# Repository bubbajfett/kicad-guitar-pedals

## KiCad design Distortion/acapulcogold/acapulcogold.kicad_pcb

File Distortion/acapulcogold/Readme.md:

# Acapulco Gold Distorgion

This is a clone of the Earthquaker Devices acapulco gold distortion pedal.

It is base on  a pair of LM386 op-amps, and provides a very crunchy distortion.

So this pedal is verified. I have not boxed this one yet, either.

All trademarks belong to their respective owners.

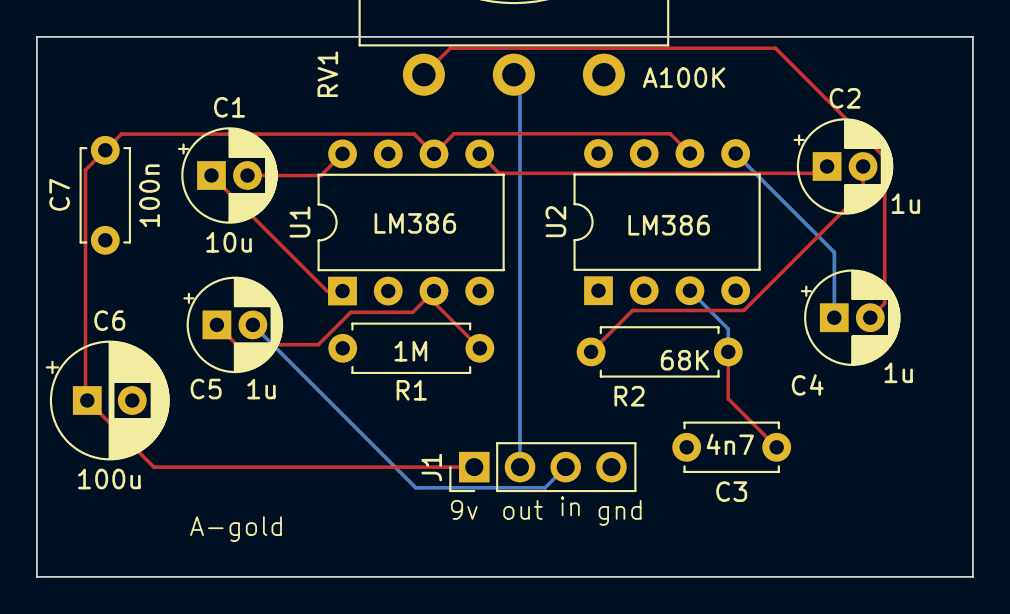
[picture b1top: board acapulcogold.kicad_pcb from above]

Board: 2 copper layers, 52.0 x 30.0 mm, 13 parts (0 on the bottom side), 12 nets.

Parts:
C1: 10u; CP_Radial_D5.0mm_P2.00mm
C2, C4, C5: 1u; CP_Radial_D5.0mm_P2.00mm
C3: 4n7; C_Disc_D5.0mm_W2.5mm_P5.00mm
C6: 100u; CP_Radial_D6.3mm_P2.50mm
C7: 100n; C_Disc_D5.0mm_W2.5mm_P5.00mm
J1: Conn_01x04_Pin; PinHeader_1x04_P2.54mm_Vertical
R1: 1M; R_Axial_DIN0207_L6.3mm_D2.5mm_P7.62mm_Horizontal
R2: 68K; R_Axial_DIN0207_L6.3mm_D2.5mm_P7.62mm_Horizontal
RV1: A100K; Potentiometer_Omeg_PC16BU_Vertical
U1, U2: LM386; DIP-8_W7.62mm

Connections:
GND: C3.2, C6.2, C7.1, J1.4, R1.2, RV1.1, U1.2 (-), U1.4 (GND), U2.2 (-), U2.4 (GND)
unnamed: C1.1, U1.1 (GAIN)
unnamed: C1.2, U1.8 (GAIN)
unnamed: C2.1, U1.5
unnamed: C2.2, R2.1
unnamed: C4.1, U2.5
unnamed: C4.2, RV1.3
unnamed: C5.1, R1.1, U1.3 (+)
unnamed: C3.1, R2.2, U2.3 (+)
in: C5.2, J1.3
out: J1.2, RV1.2
vcc: C6.1, C7.2, J1.1, U1.6 (V+), U2.6 (V+)

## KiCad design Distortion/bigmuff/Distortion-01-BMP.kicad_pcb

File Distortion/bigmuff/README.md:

# big muff

Distortion pedal, loosely based on BMP

Two PCB layouts now, one is for unclear version of BMP, and the
other based on the ramshead version.   Both sound pretty
much the same to me.   The
ramshead version uses different potentiometer form-factor (RK09).  

Both are verified.

Requires KICAD 7

Build doc is [here](./bigmuff.pdf)

All trademarks are owned by their respective owners.

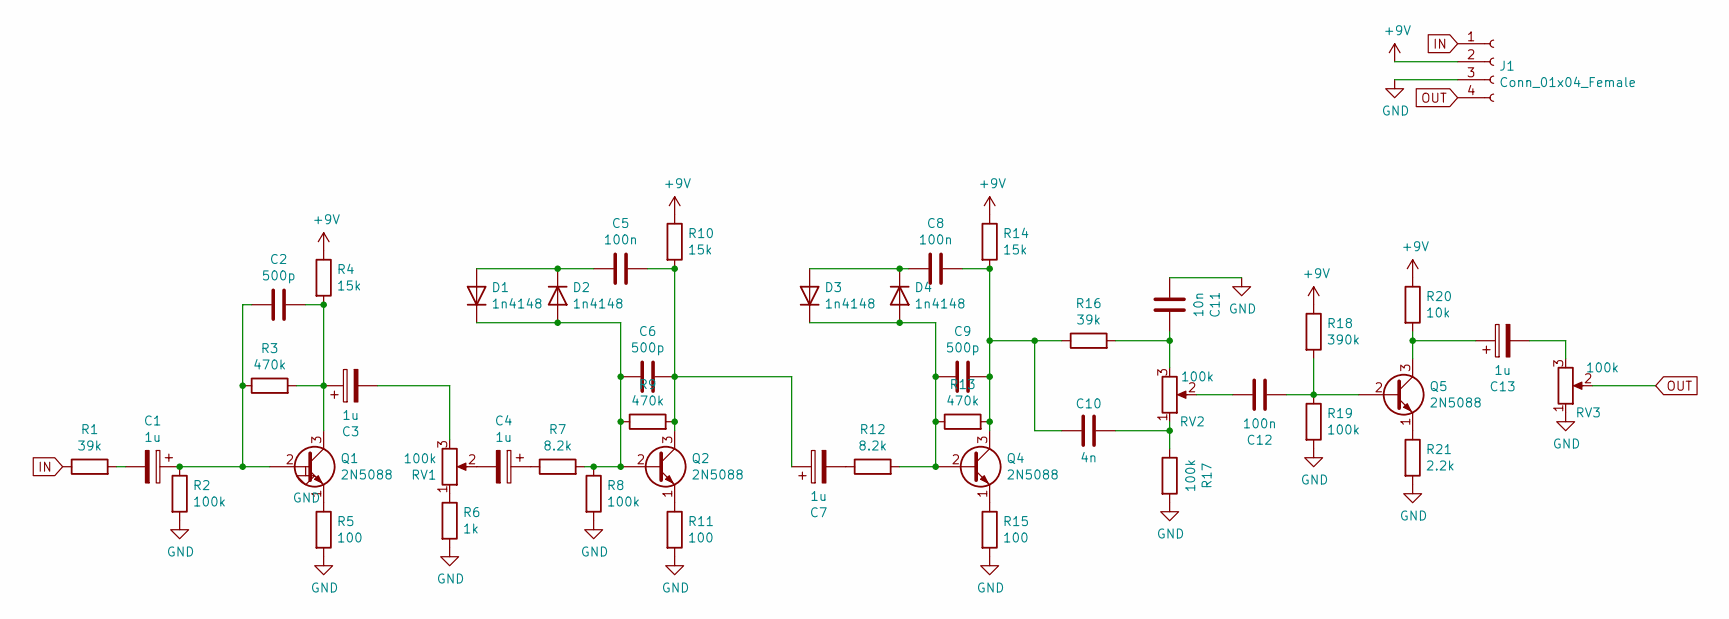
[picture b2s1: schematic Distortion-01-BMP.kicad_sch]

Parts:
C1, C3, C4, C7, C13: 1u; CP_Radial_D5.0mm_P2.00mm
C2, C6, C9: 500p; C_Disc_D7.5mm_W2.5mm_P5.00mm
C5, C8, C12: 100n; C_Disc_D7.5mm_W2.5mm_P5.00mm
C10: 4n; C_Disc_D7.5mm_W2.5mm_P5.00mm
C11: 10n; C_Disc_D7.5mm_W2.5mm_P5.00mm
D1, D2, D3, D4: 1n4148; D_A-405_P7.62mm_Horizontal
J1: Conn_01x04_Female; PinHeader_1x04_P2.54mm_Vertical
Q1, Q2, Q4, Q5: 2N5088; TO-92_Inline
R1, R16: 39k; R_Axial_DIN0207_L6.3mm_D2.5mm_P10.16mm_Horizontal
R2, R8, R17, R19: 100k; R_Axial_DIN0207_L6.3mm_D2.5mm_P10.16mm_Horizontal
R3, R9, R13: 470k; R_Axial_DIN0207_L6.3mm_D2.5mm_P10.16mm_Horizontal
R4, R10, R14: 15k; R_Axial_DIN0207_L6.3mm_D2.5mm_P10.16mm_Horizontal
R5, R11, R15: 100; R_Axial_DIN0207_L6.3mm_D2.5mm_P10.16mm_Horizontal
R6: 1k; R_Axial_DIN0207_L6.3mm_D2.5mm_P10.16mm_Horizontal
R7, R12: 8.2k; R_Axial_DIN0207_L6.3mm_D2.5mm_P10.16mm_Horizontal
R18: 390k; R_Axial_DIN0207_L6.3mm_D2.5mm_P10.16mm_Horizontal
R20: 10k; R_Axial_DIN0207_L6.3mm_D2.5mm_P10.16mm_Horizontal
R21: 2.2k; R_Axial_DIN0207_L6.3mm_D2.5mm_P10.16mm_Horizontal
RV1, RV2, RV3: 100k; Potentiometer_Omeg_PC16BU_Vertical

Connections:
+9V: J1.2, R4.1, R10.1, R14.1, R18.1, R20.1
GND: C11.2, J1.3, R2.2, R5.2, R6.2, R8.2, R11.2, R15.2, R17.2, R19.2, R21.2, RV3.1
IN: J1.1, R1.1
unnamed: C1.1, C2.2, Q1.2 (B), R2.1, R3.1
unnamed: C1.2, R1.2
unnamed: C2.1, C3.1, Q1.3 (C), R3.2, R4.2
unnamed: C3.2, RV1.3
unnamed: C4.1, R7.1
unnamed: C4.2, RV1.2
unnamed: C5.1, C6.1, C7.1, Q2.3 (C), R9.2, R10.2
unnamed: C5.2, D1.2 (A), D2.1 (K)
unnamed: C6.2, D1.1 (K), D2.2 (A), Q2.2 (B), R7.2, R8.1, R9.1
unnamed: C7.2, R12.1
unnamed: C8.2, D3.2 (A), D4.1 (K)
unnamed: C9.2, D3.1 (K), D4.2 (A), Q4.2 (B), R12.2, R13.1
unnamed: C10.1, R17.1, RV2.1
unnamed: C8.1, C9.1, C10.2, Q4.3 (C), R13.2, R14.2, R16.1
unnamed: C11.1, R16.2, RV2.3
unnamed: C12.1, RV2.2
unnamed: C12.2, Q5.2 (B), R18.2, R19.1
unnamed: C13.1, Q5.3 (C), R20.2
unnamed: C13.2, RV3.3
unnamed: Q1.1 (E), R5.1
unnamed: Q2.1 (E), R11.1
unnamed: Q4.1 (E), R15.1
unnamed: Q5.1 (E), R21.1
unnamed: R6.1, RV1.1
OUT: J1.4, RV3.2

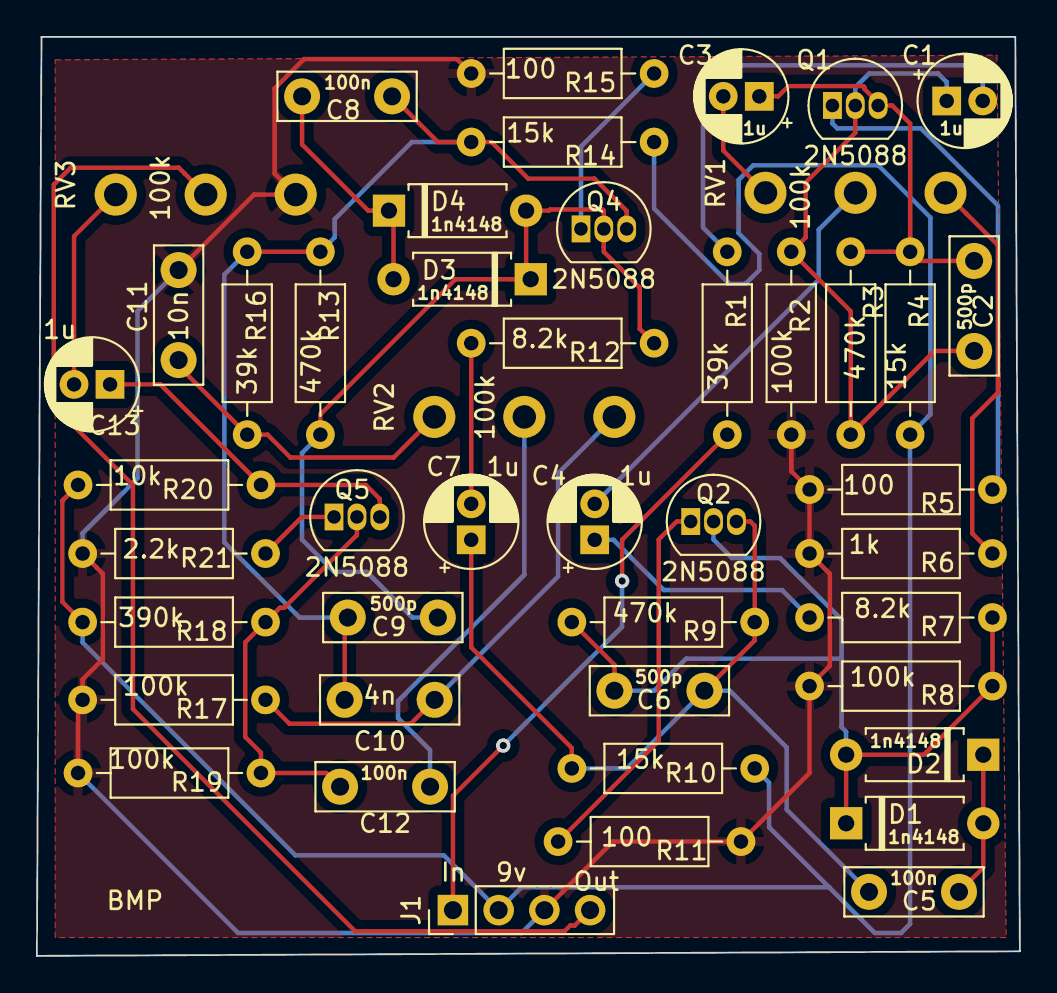
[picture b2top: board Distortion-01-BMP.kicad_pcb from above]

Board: 2 copper layers, 54.6 x 51.1 mm, 46 parts (0 on the bottom side), 28 nets.

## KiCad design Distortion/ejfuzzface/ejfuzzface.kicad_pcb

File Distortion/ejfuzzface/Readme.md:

# EJ Fuzz Face

This is a clone of the Eric Johnson fuzz face.   Very nice sound, and gets very
crunchy when first in the chain.

This is the 2nd version of the pedal.   The first version had the fuzz pot without a ground connection 

So this pedal circuit  is verified.  I hate using a 125B box on something
this small but my last attempt at boxing top-jacks on a 1590B did not work very well.

Anyway, all trademarks belong to their respective owners.

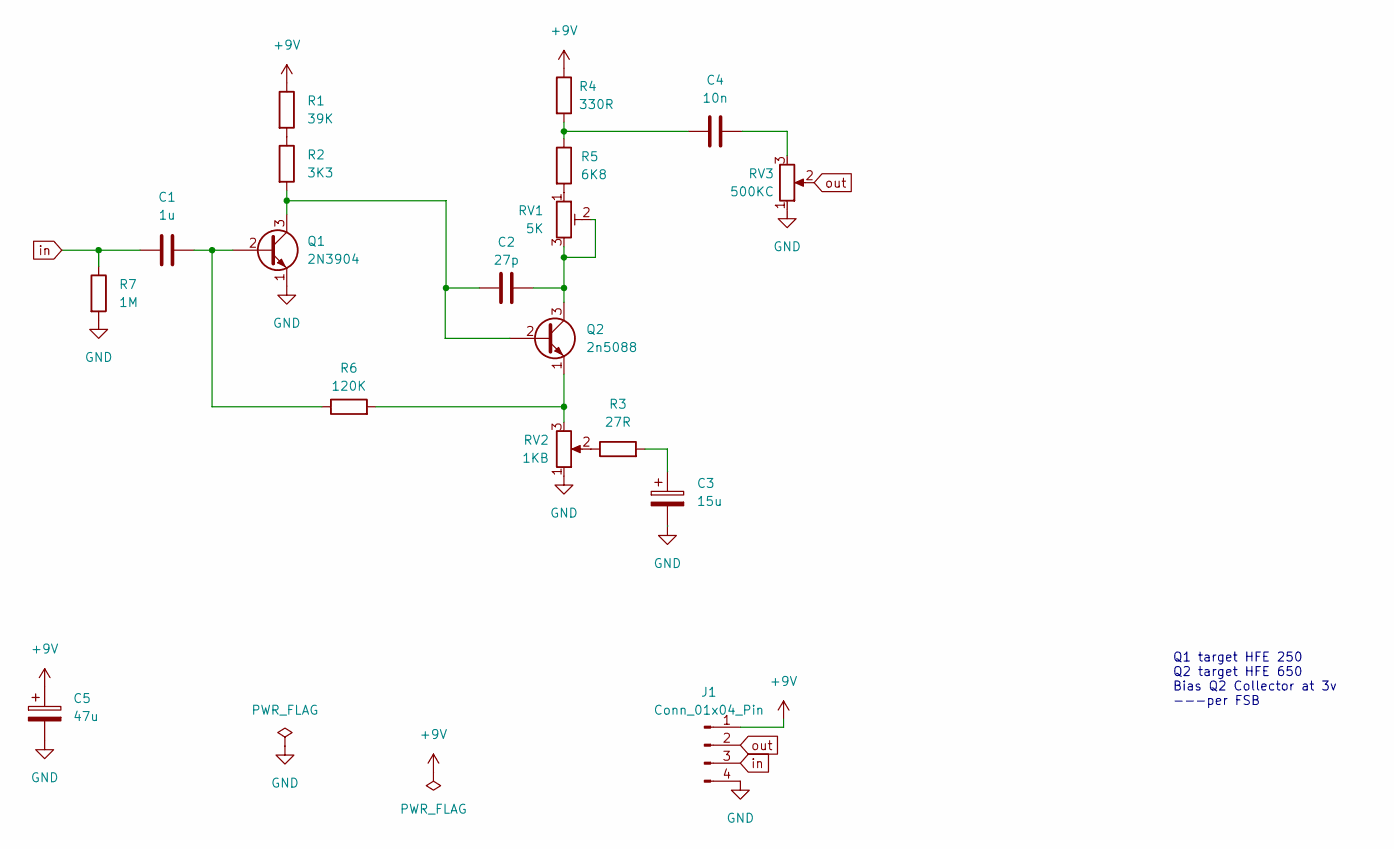
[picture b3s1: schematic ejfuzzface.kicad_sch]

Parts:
C1: 1u; C_Rect_L7.0mm_W2.0mm_P5.00mm
C2: 27p; C_Disc_D5.0mm_W2.5mm_P2.50mm
C3: 15u; CP_Radial_D6.3mm_P2.50mm
C4: 10n; C_Rect_L7.0mm_W2.0mm_P5.00mm
C5: 47u; CP_Radial_D6.3mm_P2.50mm
J1: Conn_01x04_Pin; PinHeader_1x04_P2.54mm_Vertical
Q1: 2N3904; TO-92_Inline
Q2: 2n5088; TO-92_Inline
R1: 39K; R_Axial_DIN0207_L6.3mm_D2.5mm_P10.16mm_Horizontal
R2: 3K3; R_Axial_DIN0207_L6.3mm_D2.5mm_P10.16mm_Horizontal
R3: 27R; R_Axial_DIN0207_L6.3mm_D2.5mm_P10.16mm_Horizontal
R4: 330R; R_Axial_DIN0207_L6.3mm_D2.5mm_P10.16mm_Horizontal
R5: 6K8; R_Axial_DIN0207_L6.3mm_D2.5mm_P10.16mm_Horizontal
R6: 120K; R_Axial_DIN0207_L6.3mm_D2.5mm_P10.16mm_Horizontal
R7: 1M; R_Axial_DIN0207_L6.3mm_D2.5mm_P10.16mm_Horizontal
RV1: 5K; Potentiometer_Runtron_RM-065_Vertical
RV2: 1KB; Pot_Underside
RV3: 500KC; Pot_Underside

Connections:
+9V: C5.1, J1.1, R1.1, R4.1
GND: C3.2, C5.2, J1.4, Q1.1 (E), R7.2, RV2.1, RV3.1
unnamed: C3.1, R3.2
unnamed: C4.1, R4.2, R5.1
unnamed: C4.2, RV3.3
unnamed: C1.2, Q1.2 (B), R6.1
unnamed: C2.1, Q1.3 (C), Q2.2 (B), R2.2
unnamed: C2.2, Q2.3 (C), RV1.2, RV1.3
unnamed: Q2.1 (E), R6.2, RV2.3
unnamed: R1.2, R2.1
unnamed: R3.1, RV2.2
unnamed: R5.2, RV1.1
in: C1.1, J1.3, R7.1
out: J1.2, RV3.2

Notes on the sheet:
Q1 target HFE 250 Q2 target HFE 650 Bias Q2 Collector at 3v ---per FSB

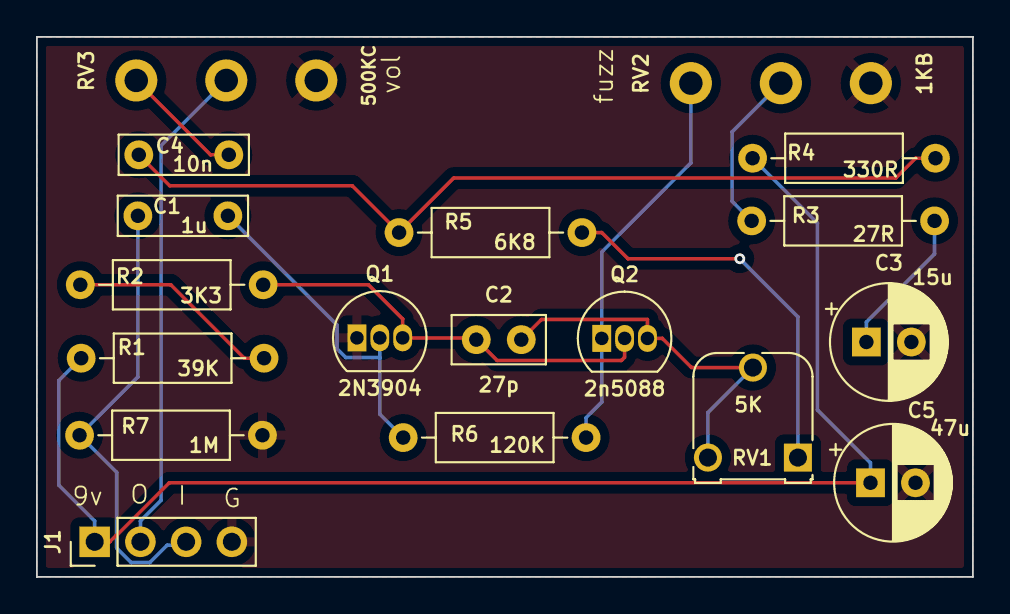
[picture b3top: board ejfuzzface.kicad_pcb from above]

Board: 2 copper layers, 52.0 x 30.0 mm, 18 parts (0 on the bottom side), 14 nets.

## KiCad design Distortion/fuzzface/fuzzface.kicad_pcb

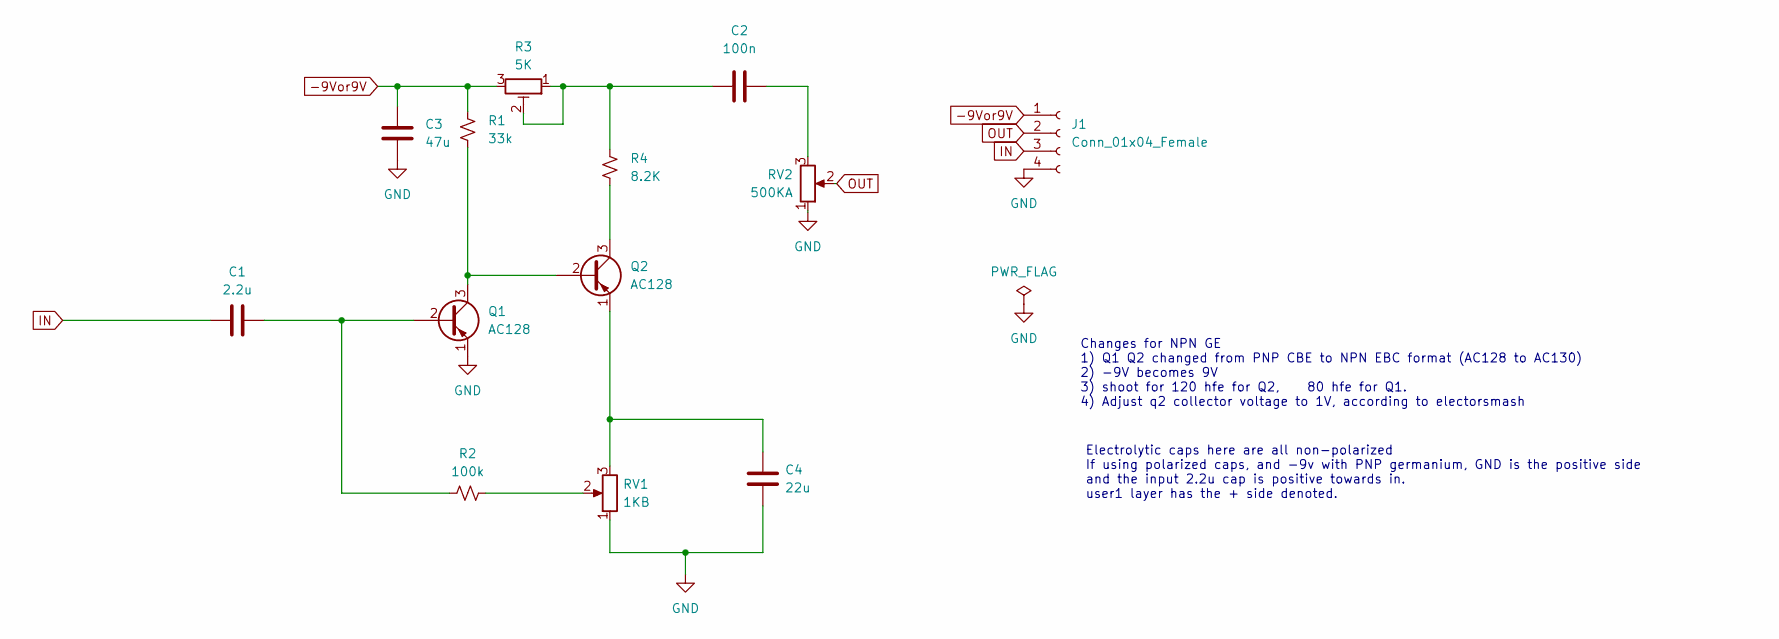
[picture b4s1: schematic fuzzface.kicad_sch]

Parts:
C1: 2.2u; C_Radial_D5.0mm_H5.0mm_P2.00mm
C2: 100n; C_Rect_L7.0mm_W3.5mm_P5.00mm
C3: 47u; C_Radial_D6.3mm_H7.0mm_P2.50mm
C4: 22u; C_Radial_D6.3mm_H7.0mm_P2.50mm
J1: Conn_01x04_Female; PinHeader_1x04_P2.54mm_Vertical
Q1, Q2: AC128; PinHeader_1x03_P2.54mm_Vertical
R1: 33k; R_Axial_DIN0207_L6.3mm_D2.5mm_P10.16mm_Horizontal
R2: 100k; R_Axial_DIN0207_L6.3mm_D2.5mm_P10.16mm_Horizontal
R3: 5K; Potentiometer_Runtron_RM-065_Vertical
R4: 8.2K; R_Axial_DIN0207_L6.3mm_D2.5mm_P10.16mm_Horizontal
RV1: 1KB; 16MM_PCB_PADS
RV2: 500KA; 16MM_PCB_PADS

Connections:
-9Vor9V: C3.1, J1.1, R1.2, R3.3
GND: C3.2, C4.2, J1.4, Q1.1 (E), RV1.1, RV2.1
IN: C1.1, J1.3
unnamed: C2.1, R3.1, R3.2, R4.2
unnamed: C2.2, RV2.3
unnamed: C1.2, Q1.2 (B), R2.1
unnamed: Q1.3 (C), Q2.2 (B), R1.1
unnamed: Q2.3 (C), R4.1
unnamed: C4.1, Q2.1 (E), RV1.3
unnamed: R2.2, RV1.2
OUT: J1.2, RV2.2

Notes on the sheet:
Electrolytic caps here are all non-polarized If using polarized caps, and -9v with PNP germanium, GND is the positive side and the input 2.2u cap is positive towards in. user1 layer has the + side denoted.
Changes for NPN GE 1) Q1 Q2 changed from PNP CBE to NPN EBC format (AC128 to AC130) 2) -9V becomes 9V 3) shoot for 120 hfe for Q2, 80 hfe for Q1. 4) Adjust q2 collector voltage to 1V, according to electorsmash

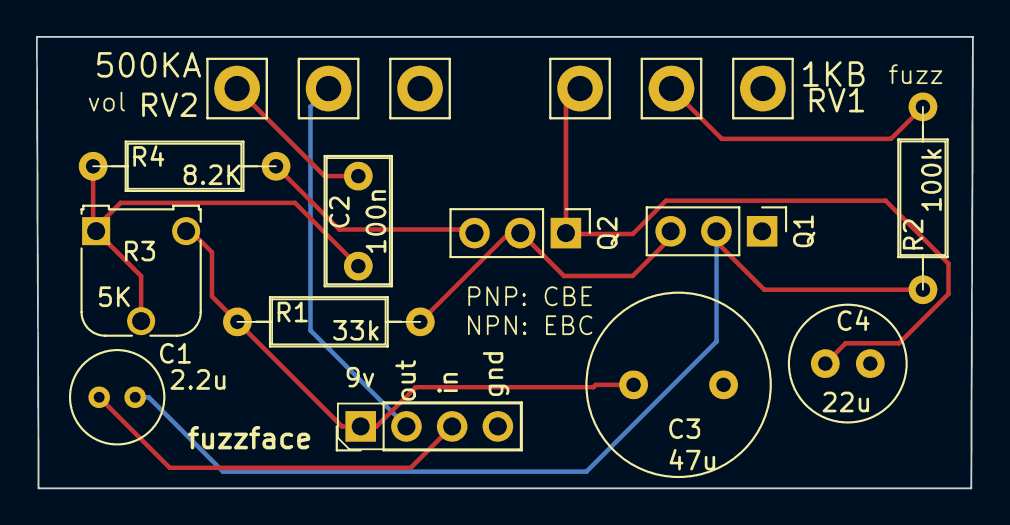
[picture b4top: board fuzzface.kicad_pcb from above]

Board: 2 copper layers, 52.0 x 25.1 mm, 13 parts (0 on the bottom side), 11 nets.

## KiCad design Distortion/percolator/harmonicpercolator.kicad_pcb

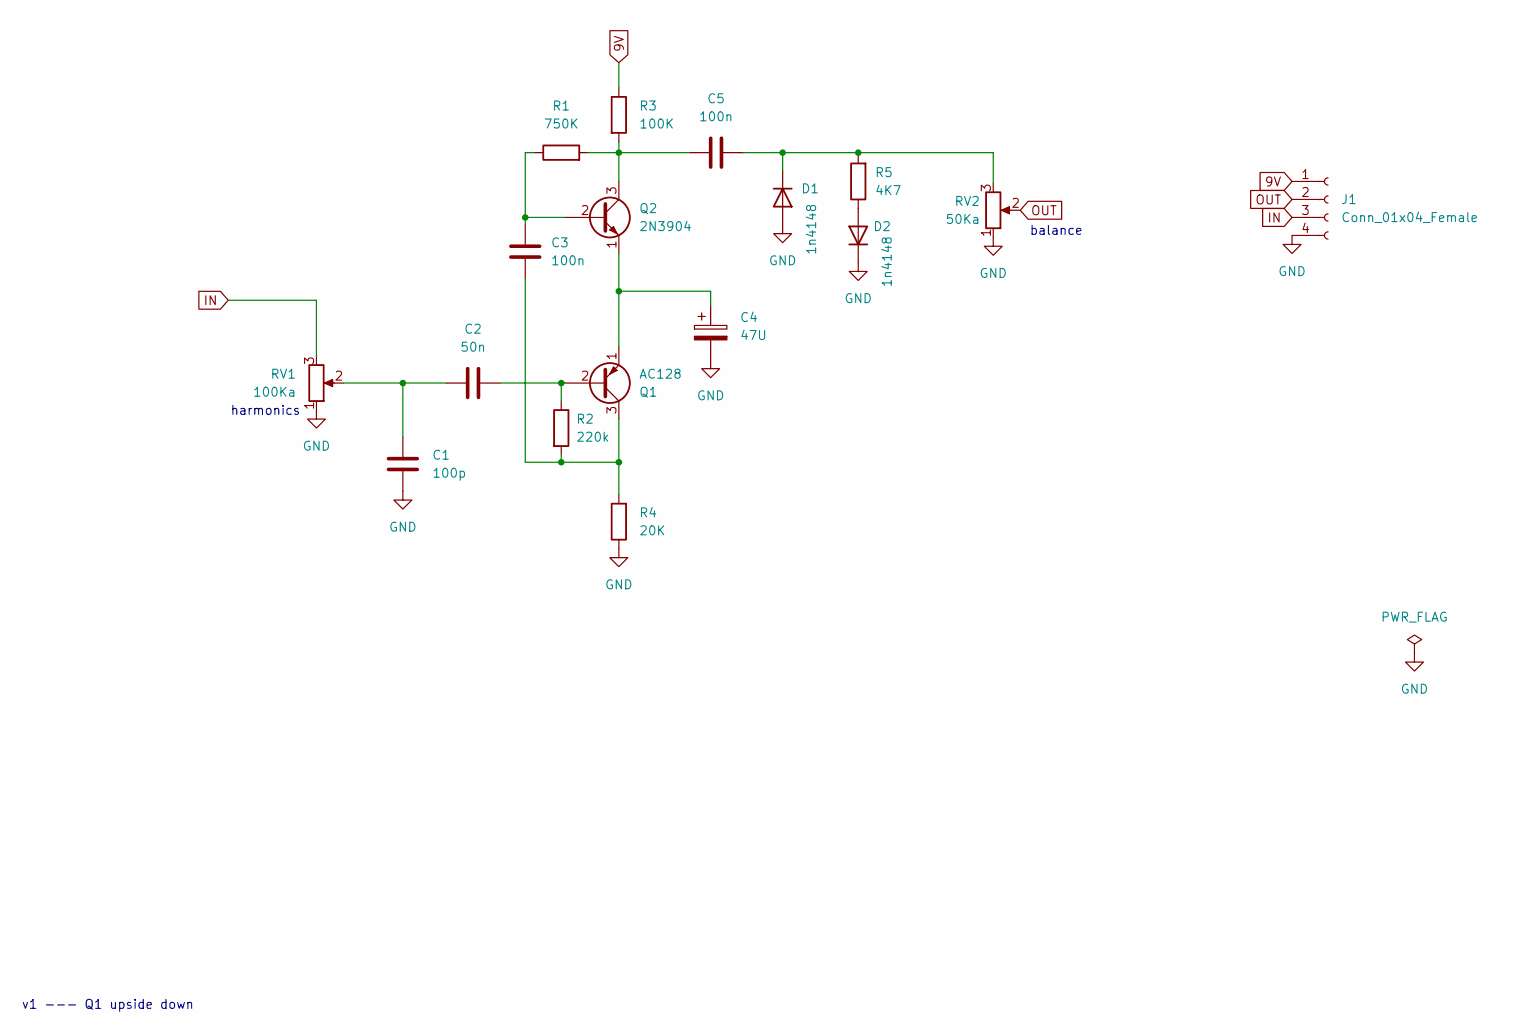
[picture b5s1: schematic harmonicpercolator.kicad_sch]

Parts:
C1: 100p; C_Disc_D5.0mm_W2.5mm_P2.50mm
C2: 50n; C_Disc_D7.5mm_W2.5mm_P5.00mm
C3, C5: 100n; C_Disc_D7.5mm_W2.5mm_P5.00mm
C4: 47U; CP_Radial_D5.0mm_P2.50mm
D1, D2: 1n4148; D_A-405_P7.62mm_Horizontal
J1: Conn_01x04_Female; PinHeader_1x04_P2.54mm_Vertical
Q1: AC128; TO-5-3
Q2: 2N3904; TO-92_Inline
R1: 750K; R_Axial_DIN0207_L6.3mm_D2.5mm_P7.62mm_Horizontal
R2: 220k; R_Axial_DIN0207_L6.3mm_D2.5mm_P7.62mm_Horizontal
R3: 100K; R_Axial_DIN0207_L6.3mm_D2.5mm_P7.62mm_Horizontal
R4: 20K; R_Axial_DIN0207_L6.3mm_D2.5mm_P7.62mm_Horizontal
R5: 4K7; R_Axial_DIN0207_L6.3mm_D2.5mm_P7.62mm_Horizontal
RV1: 100Ka; Pot_Underside
RV2: 50Ka; Pot_Underside

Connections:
9V: J1.1, R3.1
GND: C1.2, C4.2, D1.2 (A), D2.1 (K), J1.4, R4.1, RV1.1, RV2.1
IN: J1.3, RV1.3
unnamed: C1.1, C2.1, RV1.2
unnamed: C5.1, D1.1 (K), R5.2, RV2.3
unnamed: D2.2 (A), R5.1
unnamed: C2.2, Q1.2 (B), R2.1
unnamed: C3.1, Q1.3 (C), R2.2, R4.2
unnamed: C4.1, Q1.1 (E), Q2.1 (E)
unnamed: C3.2, Q2.2 (B), R1.1
unnamed: C5.2, Q2.3 (C), R1.2, R3.2
OUT: J1.2, RV2.2

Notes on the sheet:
balance
harmonics
v1 --- Q1 upside down

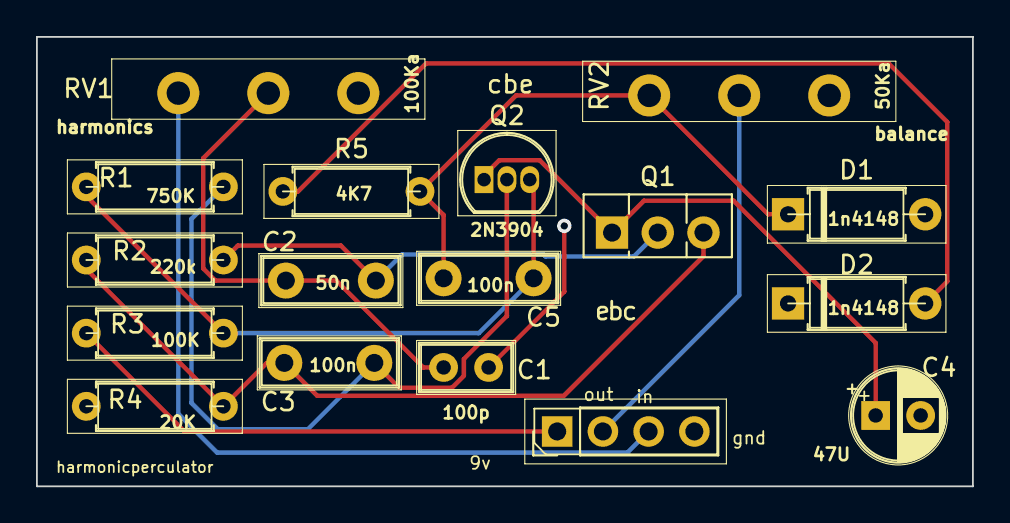
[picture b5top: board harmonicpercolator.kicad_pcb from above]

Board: 2 copper layers, 52.0 x 25.0 mm, 17 parts (0 on the bottom side), 12 nets.

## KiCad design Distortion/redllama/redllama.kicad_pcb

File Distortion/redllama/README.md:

Distortion pedal, loosely based on the red llama pedal.

This is unverified.

All trademarks belong to their respective trademark owners.

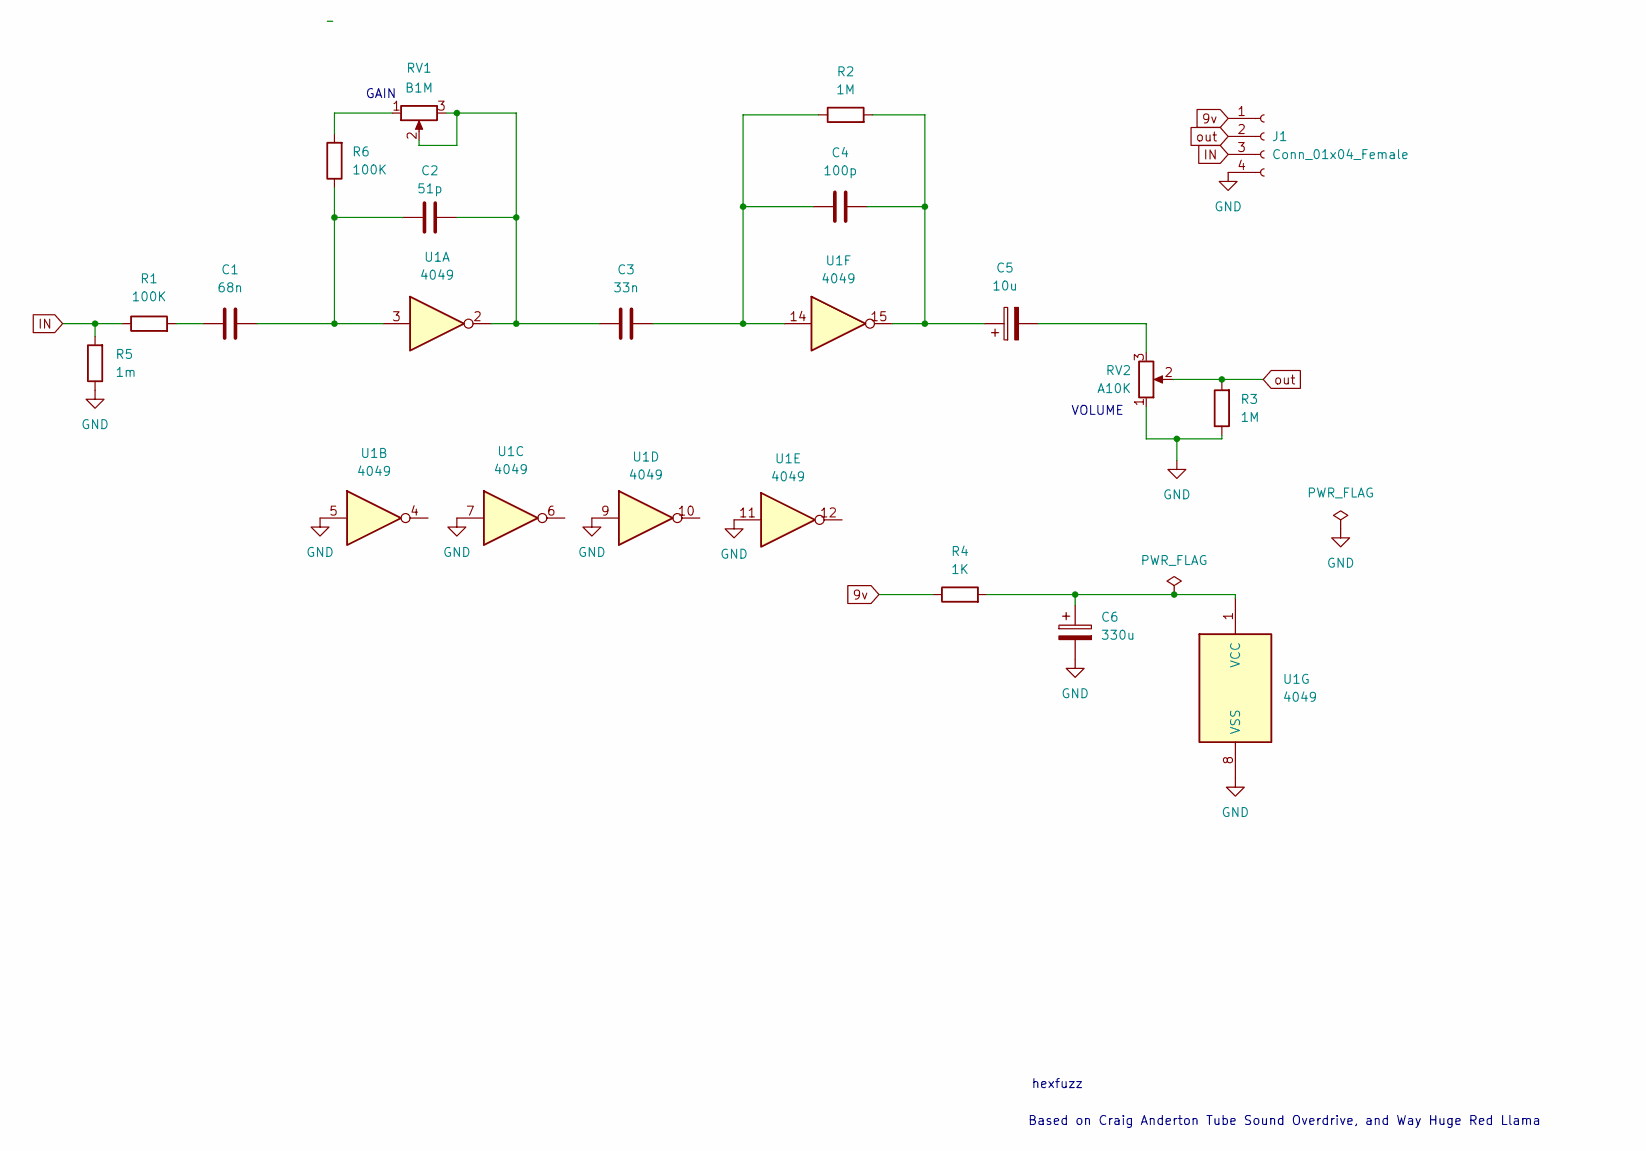
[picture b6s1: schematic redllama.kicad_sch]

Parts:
C1: 68n; C_Rect_L7.0mm_W2.5mm_P5.00mm
C2: 51p; C_Disc_D3.8mm_W2.6mm_P2.50mm
C3: 33n; C_Rect_L7.0mm_W2.5mm_P5.00mm
C4: 100p; C_Disc_D3.8mm_W2.6mm_P2.50mm
C5: 10u; CP_Radial_D5.0mm_P2.00mm
C6: 330u; CP_Radial_D7.5mm_P2.50mm
J1: Conn_01x04_Female; PinHeader_1x04_P2.54mm_Vertical
R1, R6: 100K; R_Axial_DIN0207_L6.3mm_D2.5mm_P7.62mm_Horizontal
R2, R3: 1M; R_Axial_DIN0207_L6.3mm_D2.5mm_P7.62mm_Horizontal
R4: 1K; R_Axial_DIN0207_L6.3mm_D2.5mm_P7.62mm_Horizontal
R5: 1m; R_Axial_DIN0207_L6.3mm_D2.5mm_P7.62mm_Horizontal
RV1: B1M; Pot_Underside
RV2: A10K; Pot_Underside
U1: 4049; DIP-16_W7.62mm

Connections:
9v: J1.1, R4.1
GND: C6.2, J1.4, R3.1, R5.1, RV2.1, U1.5, U1.7, U1.8 (VSS), U1.9, U1.11
IN: J1.3, R1.1, R5.2
unnamed: C1.1, R1.2
unnamed: C1.2, C2.1, R6.1, U1.3
unnamed: C2.2, C3.1, RV1.2, RV1.3, U1.2
unnamed: C3.2, C4.1, R2.1, U1.14
unnamed: C4.2, C5.1, R2.2, U1.15
unnamed: C5.2, RV2.3
unnamed: R6.2, RV1.1
unnamed: C6.1, R4.2, U1.1 (VCC)
out: J1.2, R3.2, RV2.2

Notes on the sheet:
GAIN
Based on Craig Anderton Tube Sound Overdrive, and Way Huge Red Llama
hexfuzz
VOLUME

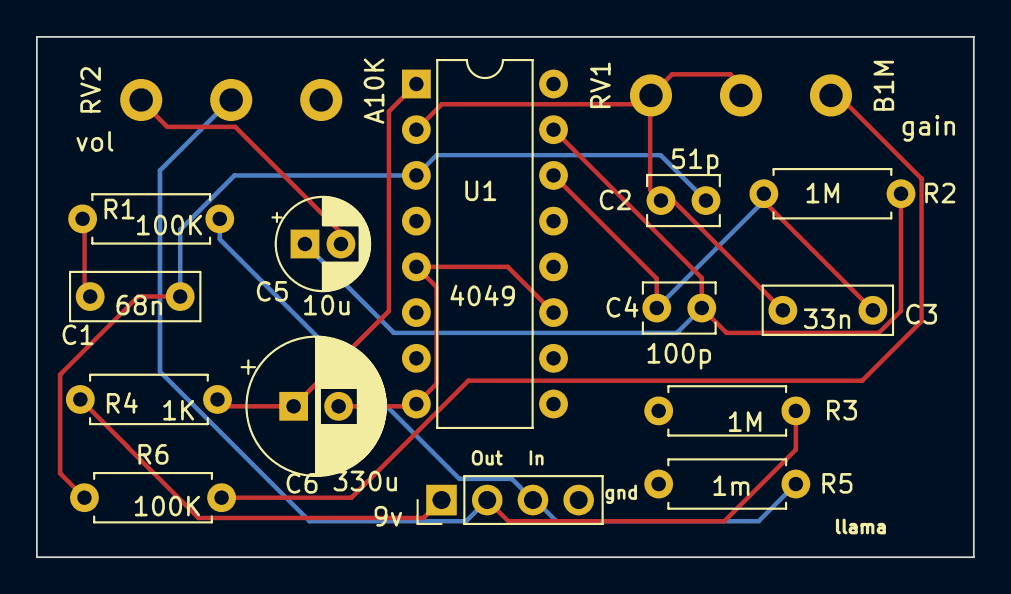
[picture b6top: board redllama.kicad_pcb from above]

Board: 2 copper layers, 52.1 x 28.9 mm, 16 parts (0 on the bottom side), 12 nets.

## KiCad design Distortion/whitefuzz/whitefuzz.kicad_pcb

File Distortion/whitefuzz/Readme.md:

# whitefuzz

This pedal is based on the Bearfoot FX artic white fuzz, which is apparently somewhat based on the fuzzface

First build used 2n5457 and while it made a distortion sound, it was
very clippy.  Researching other (dirtboxlayout, effectslayout,
pedalpcb) forums, the recommendation was to use J113 (and a couple
other jfets I did not have).  Replacing this made this sound so much
better.

All registered trademarks are owned by their respective owners.

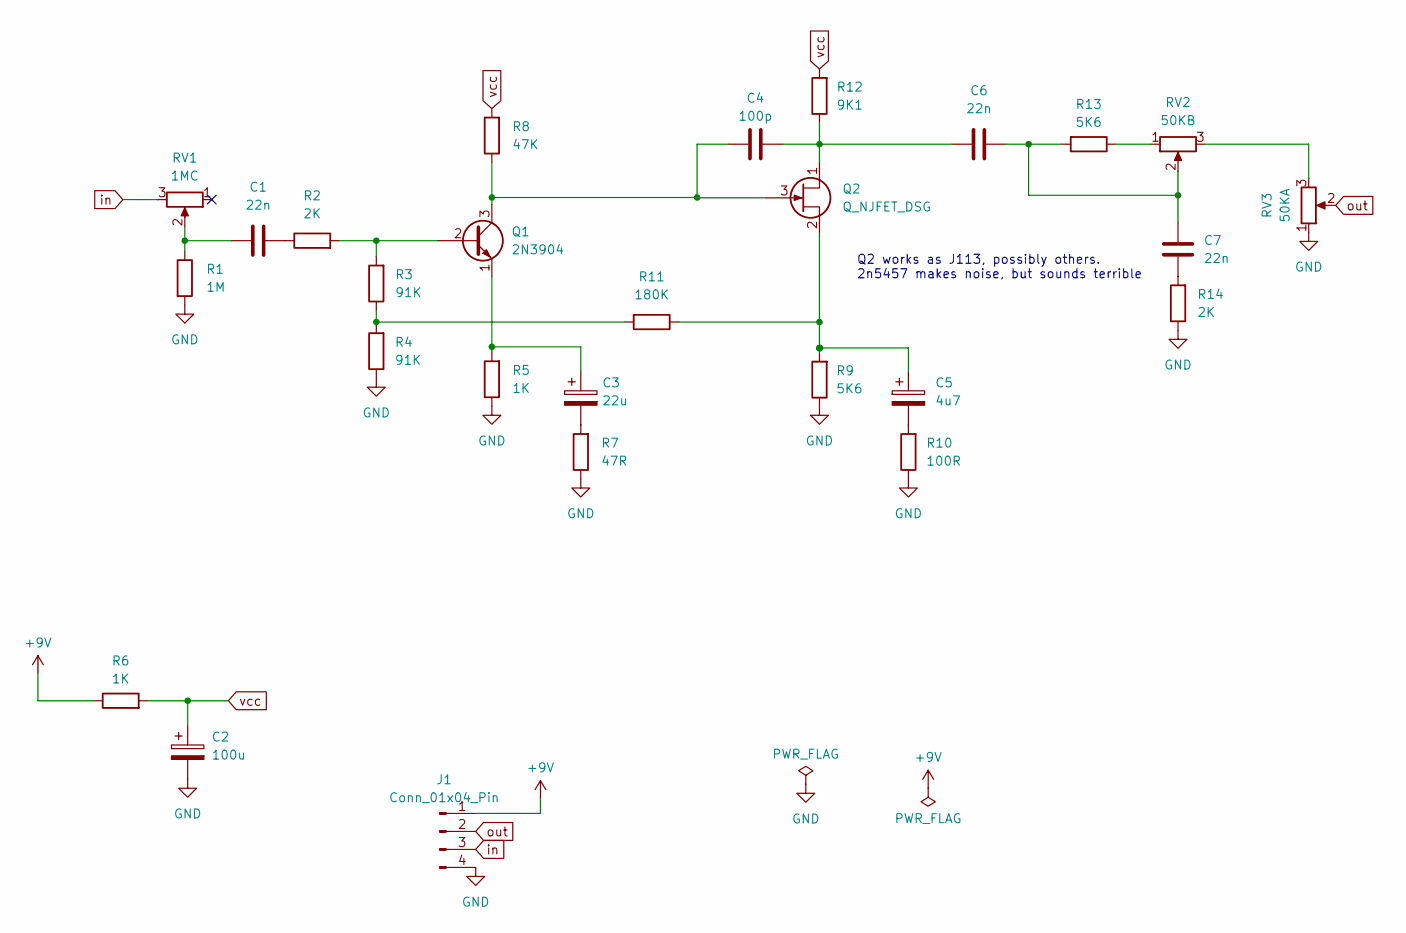
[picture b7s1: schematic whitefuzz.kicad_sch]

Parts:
C1, C6, C7: 22n; C_Rect_L7.0mm_W2.5mm_P5.00mm
C2: 100u; CP_Radial_D6.3mm_P2.50mm
C3: 22u; CP_Radial_D5.0mm_P2.00mm
C4: 100p; C_Disc_D5.0mm_W2.5mm_P2.50mm
C5: 4u7; CP_Radial_D5.0mm_P2.00mm
J1: Conn_01x04_Pin; PinHeader_1x04_P2.54mm_Vertical
Q1: 2N3904; TO-92_Inline
Q2: Q_NJFET_DSG; TO-92
R1: 1M; R_Axial_DIN0207_L6.3mm_D2.5mm_P10.16mm_Horizontal
R2, R14: 2K; R_Axial_DIN0207_L6.3mm_D2.5mm_P10.16mm_Horizontal
R3, R4: 91K; R_Axial_DIN0207_L6.3mm_D2.5mm_P10.16mm_Horizontal
R5, R6: 1K; R_Axial_DIN0207_L6.3mm_D2.5mm_P10.16mm_Horizontal
R7: 47R; R_Axial_DIN0207_L6.3mm_D2.5mm_P10.16mm_Horizontal
R8: 47K; R_Axial_DIN0207_L6.3mm_D2.5mm_P10.16mm_Horizontal
R9, R13: 5K6; R_Axial_DIN0207_L6.3mm_D2.5mm_P10.16mm_Horizontal
R10: 100R; R_Axial_DIN0207_L6.3mm_D2.5mm_P10.16mm_Horizontal
R11: 180K; R_Axial_DIN0207_L6.3mm_D2.5mm_P10.16mm_Horizontal
R12: 9K1; R_Axial_DIN0207_L6.3mm_D2.5mm_P10.16mm_Horizontal
RV1: 1MC; Pot_Underside
RV2: 50KB; Pot_Underside
RV3: 50KA; Pot_Underside

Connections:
+9V: J1.1, R6.1
GND: C2.2, J1.4, R1.2, R4.1, R5.1, R7.1, R9.1, R10.1, R14.1, RV3.1
unnamed: C1.1, R1.1, RV1.2
unnamed: C1.2, R2.1
unnamed: C3.2, R7.2
unnamed: C5.2, R10.2
unnamed: C6.2, C7.2, R13.2, RV2.2
unnamed: C7.1, R14.2
unnamed: Q1.2 (B), R2.2, R3.2
unnamed: C4.1, Q1.3 (C), Q2.3 (G), R8.1
unnamed: C3.1, Q1.1 (E), R5.2
unnamed: C4.2, C6.1, Q2.1 (D), R12.1
unnamed: C5.1, Q2.2 (S), R9.2, R11.1
unnamed: R3.1, R4.2, R11.2
unnamed: R13.1, RV2.1
unnamed: RV2.3, RV3.3
in: J1.3, RV1.3
out: J1.2, RV3.2
vcc: C2.1, R6.2, R8.2, R12.2

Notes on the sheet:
Q2 works as J113, possibly others. 2n5457 makes noise, but sounds terrible

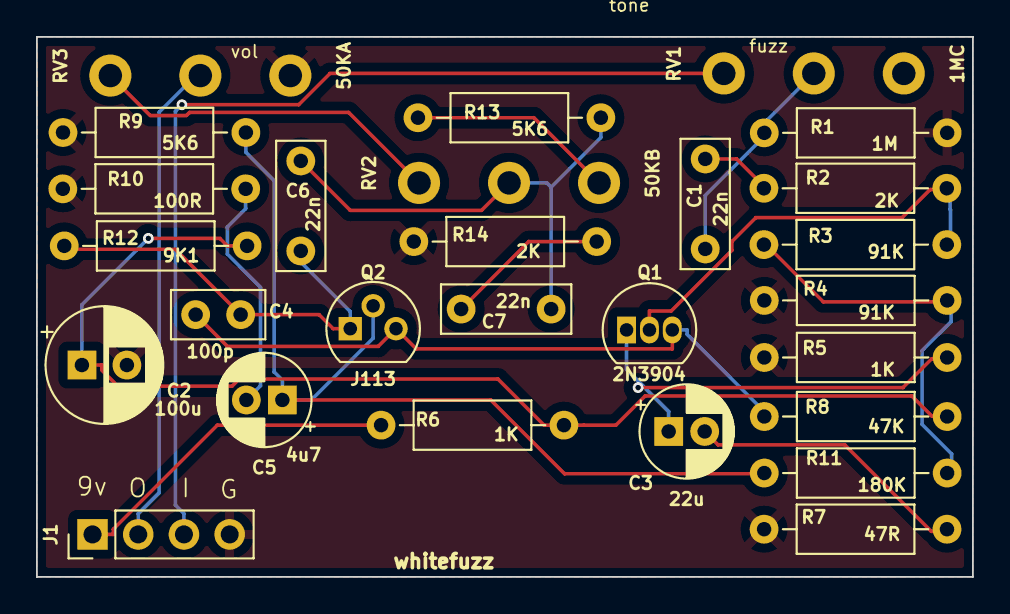
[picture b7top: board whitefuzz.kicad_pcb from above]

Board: 2 copper layers, 52.0 x 30.0 mm, 27 parts (0 on the bottom side), 19 nets.
